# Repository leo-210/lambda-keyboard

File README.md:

# Lambda keyboard

A custom 36-key wired ChocV1 split keyboard.

> Note : this keyboard is my first design, and while taking it as an inspiration
> can be a good idea, please think before building exactly this design : there
> are a few flaws that I wrote about below.

# Building the keyboard

## Components

To build the keyboard, you'll need :
- 2 RP2040-Zero micro controllers
- 2 4-pin mini DIN connectors
- 5 YS-SK6812mini-e LEDs *(optional, the keyboard will work without them)*
- 36 Kailh hot-swappable sockets
- 36 **Choc v1** (and not Choc v2 !!) switches
- 36 **Choc v1** keycaps

The keyboard is diode-less !

You can also design your own case, but I did not bother.

## Price

Ordering everything in France, including soldering tools, it cost about 110 €,
where approximately a third was for electrical components and the PCB, a second
third for key caps and switches, and the last third for shipping costs.

## Firmware

This repo also contains QMK firmware for this keyboard, using the BÉPO french
layout. The keyboard layout was inspired by
[Miryoku](https://github.com/manna-harbour/miryoku), and you can view it on
[keyboard-layout-editor.com](https://www.keyboard-layout-editor.com/#/gists/44301debdf501308d3bc676f406fde57).

# About the project

## Why design yet another split keyboard ?

I fell into the rabbit hole of custom split keyboards, and with all the summer
holidays in front of me, I couldn't hold back. It was a fun project !

I chose to make my own design because none where satisfying all my requirements,
which were :
- Exactly 36 keys, I was afraid to go with only two thumb keys, but still wanted
  to go with few keys.
- A layout with enough stagger for my pinky.

With enough research I maybe could have found something, but designing it myself
was far more interesting. 

If you want a split keyboard, you can definitely think
about creating your own ! It is not as difficult as it would seem, and this
journey is well documented and there are a lot of tools to make your life
easier.

## Why lambda ?

I like this Greek letter, and my name starts with an L.

## Inspirations 

- the [Corne keyboard](https://github.com/foostan/crkbd) and the 
  [TOTEM keyboard](https://github.com/GEIGEIGEIST/TOTEM) for the layout (among 
  others)
- [axhixh/mini-kbd](https://github.com/axhixh/mini-kbd/tree/main) which helped
  me a lot to figure out the PCB design.

## What would I change ?

As my first design, nothing is perfect, and here are some things I would change
for a future design.

### A different connector

I like that the mini DIN protects my keyboard from shorting, but the cable is
really bulky. I'll think about changing to USB C next time, or just TRRS, even
with the lack of shorting safety.

### 4 rows instead of 3 to make writing french accents easier.

Writing in English is not a problem, but in french with accents everywhere I
find it painful to constantly use layers. It is possible and can even become
reliable, but for now I couldn't really get used to it (maybe I haven't used the
keyboard enough yet...).

Also, for coding, where a lot of special symbols are needed, a couple more keys
could be useful.

### More leds

Only 5 underglow LEDs are not enough in my opinion, you can see their light but
there are some "holes". Also, for a future keyboard I'd like per key lighting as
well, even if it requires more work.

### An OLED display

Seems fun.

### Writing JLCJLCJLC on the PCB

Without this text, JLC PCB wrote a random number in a random place on my PCBs...
Fortunately it does not look that bad.

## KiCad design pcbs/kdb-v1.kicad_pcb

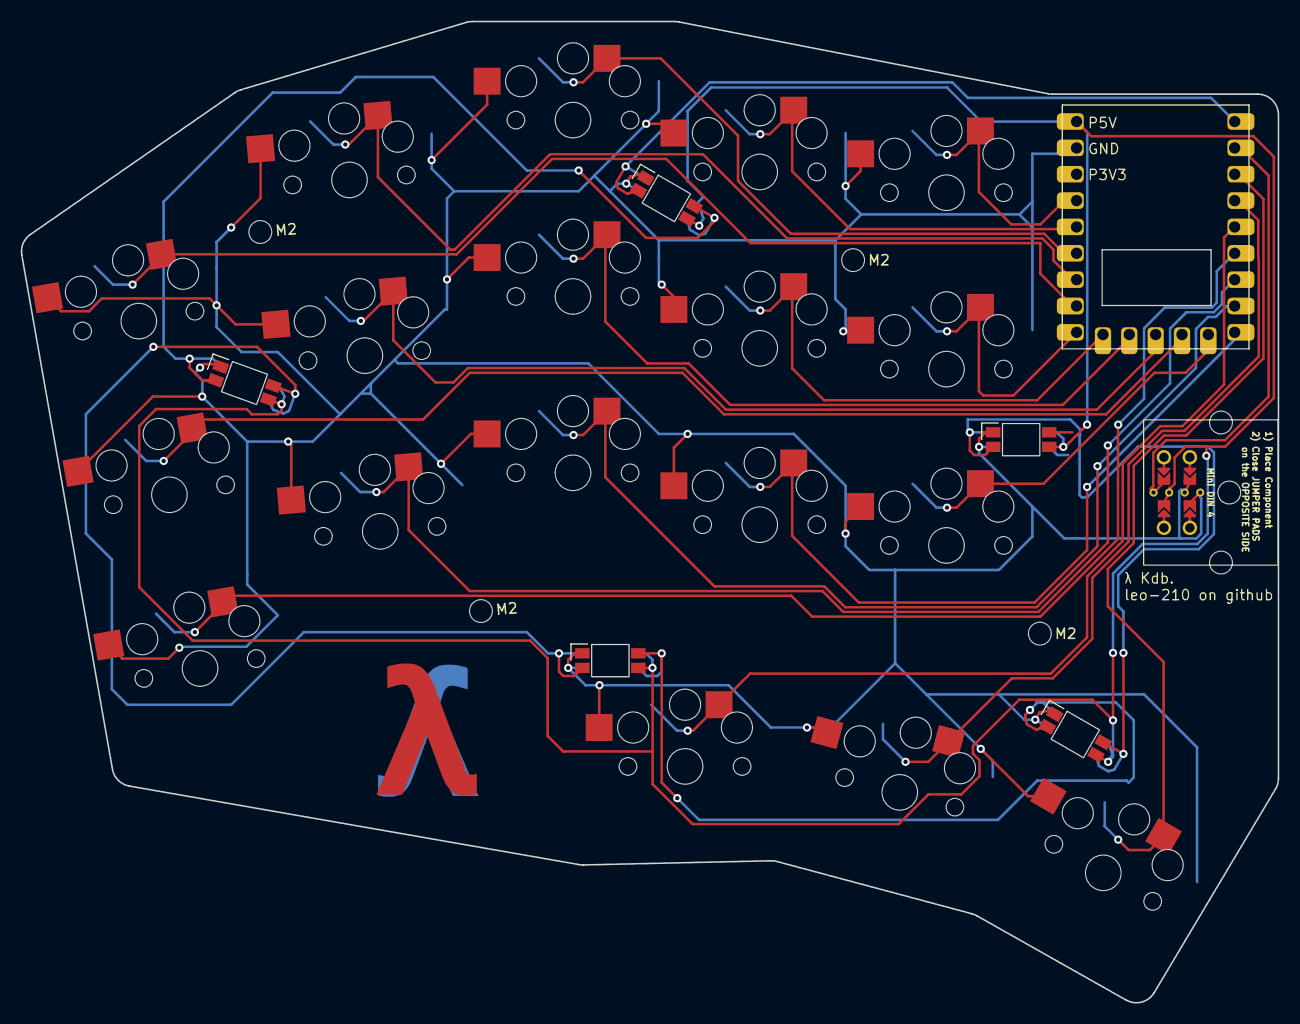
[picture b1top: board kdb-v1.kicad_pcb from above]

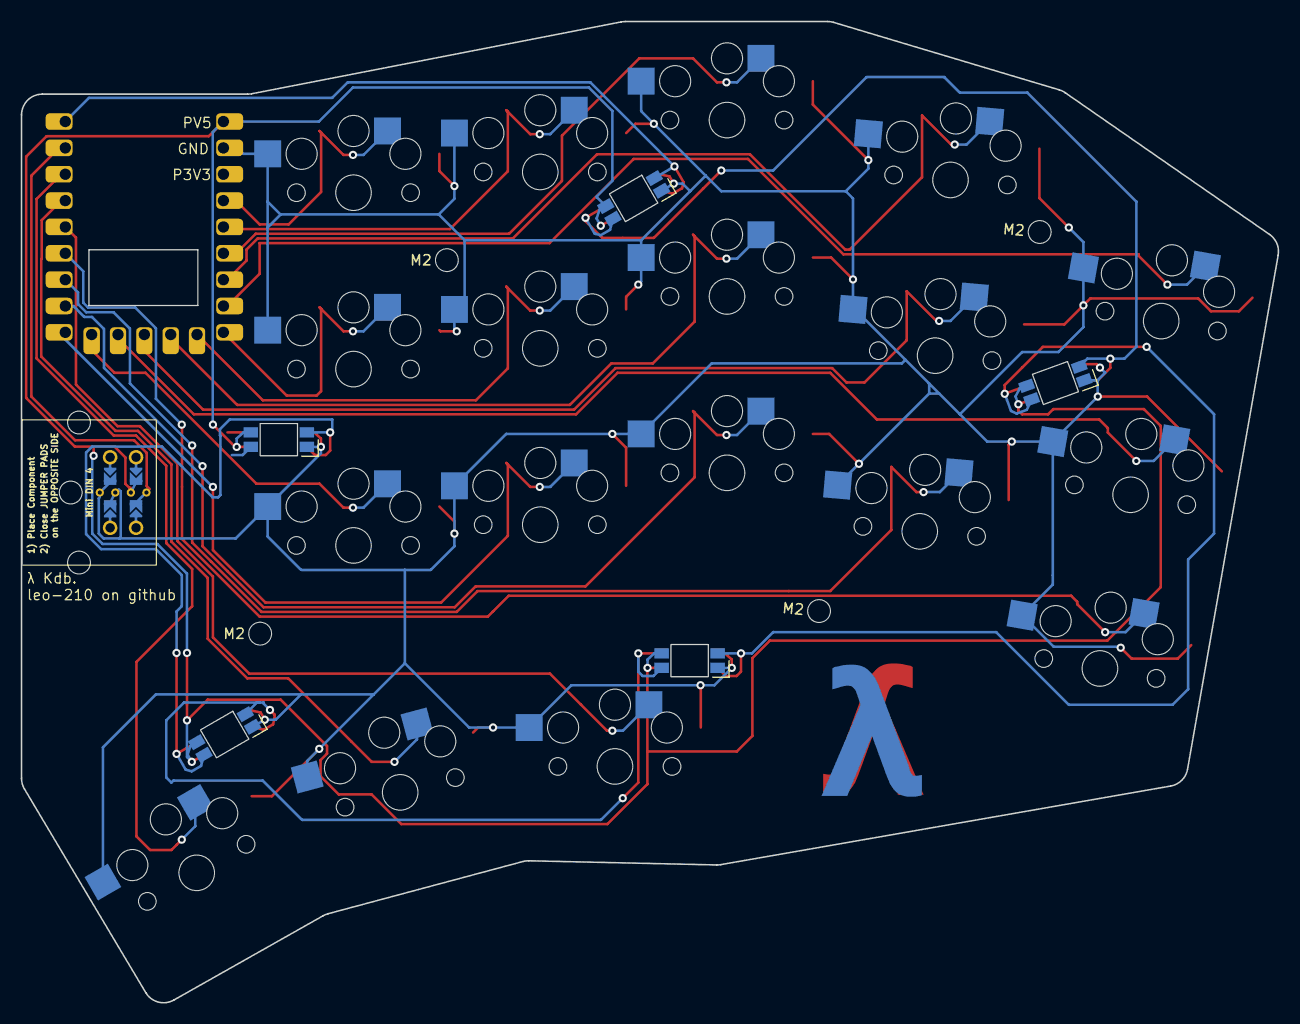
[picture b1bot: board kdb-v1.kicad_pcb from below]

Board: 2 copper layers, 121.2 x 94.6 mm, 29 parts (5 on the bottom side), 26 nets.

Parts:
AdamTech-MDJ004FS1: MiniDIN4; AdamTech_MDJ-004-FS_reversible
LED1, LED2, LED3, LED4, LED5: led_SK6812mini-e (underglow, reversible)
MH1, MH2, MH3, MH4: mounting_hole_npth
RP2040Zero1: RP2040-Zero
S1, S2, S3, S4, S5, S6, S7, S8, S9, S10, S11, S12, S13, S14, S15, S16, S17, S18: PG1350

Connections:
D1: LED1.4, LED2.2
D2: LED1.2, LED5.4
D3: LED4.4, LED5.2
D4: LED3.4, LED4.2
GND: AdamTech-MDJ004FS1.3, AdamTech-MDJ004FS1.5, LED1.3, LED2.3, LED3.3, LED4.3, LED5.3, RP2040Zero1.20, S1.2, S2.2, S3.2, S4.2, S5.2, S6.2, S7.2, S8.2, S9.2, S10.2, S11.2, S12.2, S13.2, S14.2, S15.2, S16.2, S17.2, S18.2
GP0: LED2.4, RP2040Zero1.1
GP1: AdamTech-MDJ004FS1.8, RP2040Zero1.2
GP2: RP2040Zero1.3, S18.1
GP3: RP2040Zero1.4, S17.1
GP4: RP2040Zero1.5, S16.1
GP5: RP2040Zero1.6, S1.1
GP6: RP2040Zero1.7, S4.1
GP7: RP2040Zero1.8, S7.1
GP8: RP2040Zero1.9, S10.1
GP9: RP2040Zero1.10, S13.1
GP10: RP2040Zero1.11, S2.1
GP11: RP2040Zero1.12, S5.1
GP12: RP2040Zero1.13, S8.1
GP13: RP2040Zero1.14, S11.1
GP14: RP2040Zero1.15, S14.1
GP15: RP2040Zero1.16, S3.1
GP26: RP2040Zero1.17, S6.1
GP27: RP2040Zero1.18, S9.1
GP28: RP2040Zero1.22, S12.1
GP29: RP2040Zero1.23, S15.1
P5V: AdamTech-MDJ004FS1.6, LED1.1, LED2.1, LED3.1, LED4.1, LED5.1, RP2040Zero1.19

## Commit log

2025-10-21 add firmware
2025-10-21 ignore output
2025-10-21 write readme
2025-10-21 add layout image
2025-10-21 add keyboard images
2025-10-21 enhance title
2025-12-23 fix typo
